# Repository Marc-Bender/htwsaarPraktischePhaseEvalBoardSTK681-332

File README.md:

# htwsaarPraktischePhaseEvalBoardSTK681-332
An Evaluation Board for the STK681-332-E Motor-driver IC by ON Semiconductor.
Designed as an add-on board to the arduino uno. Also designed as a concurrence "product" to the 
offical Evaluation-Board for the STK681-332-E IC with some enhanced features.

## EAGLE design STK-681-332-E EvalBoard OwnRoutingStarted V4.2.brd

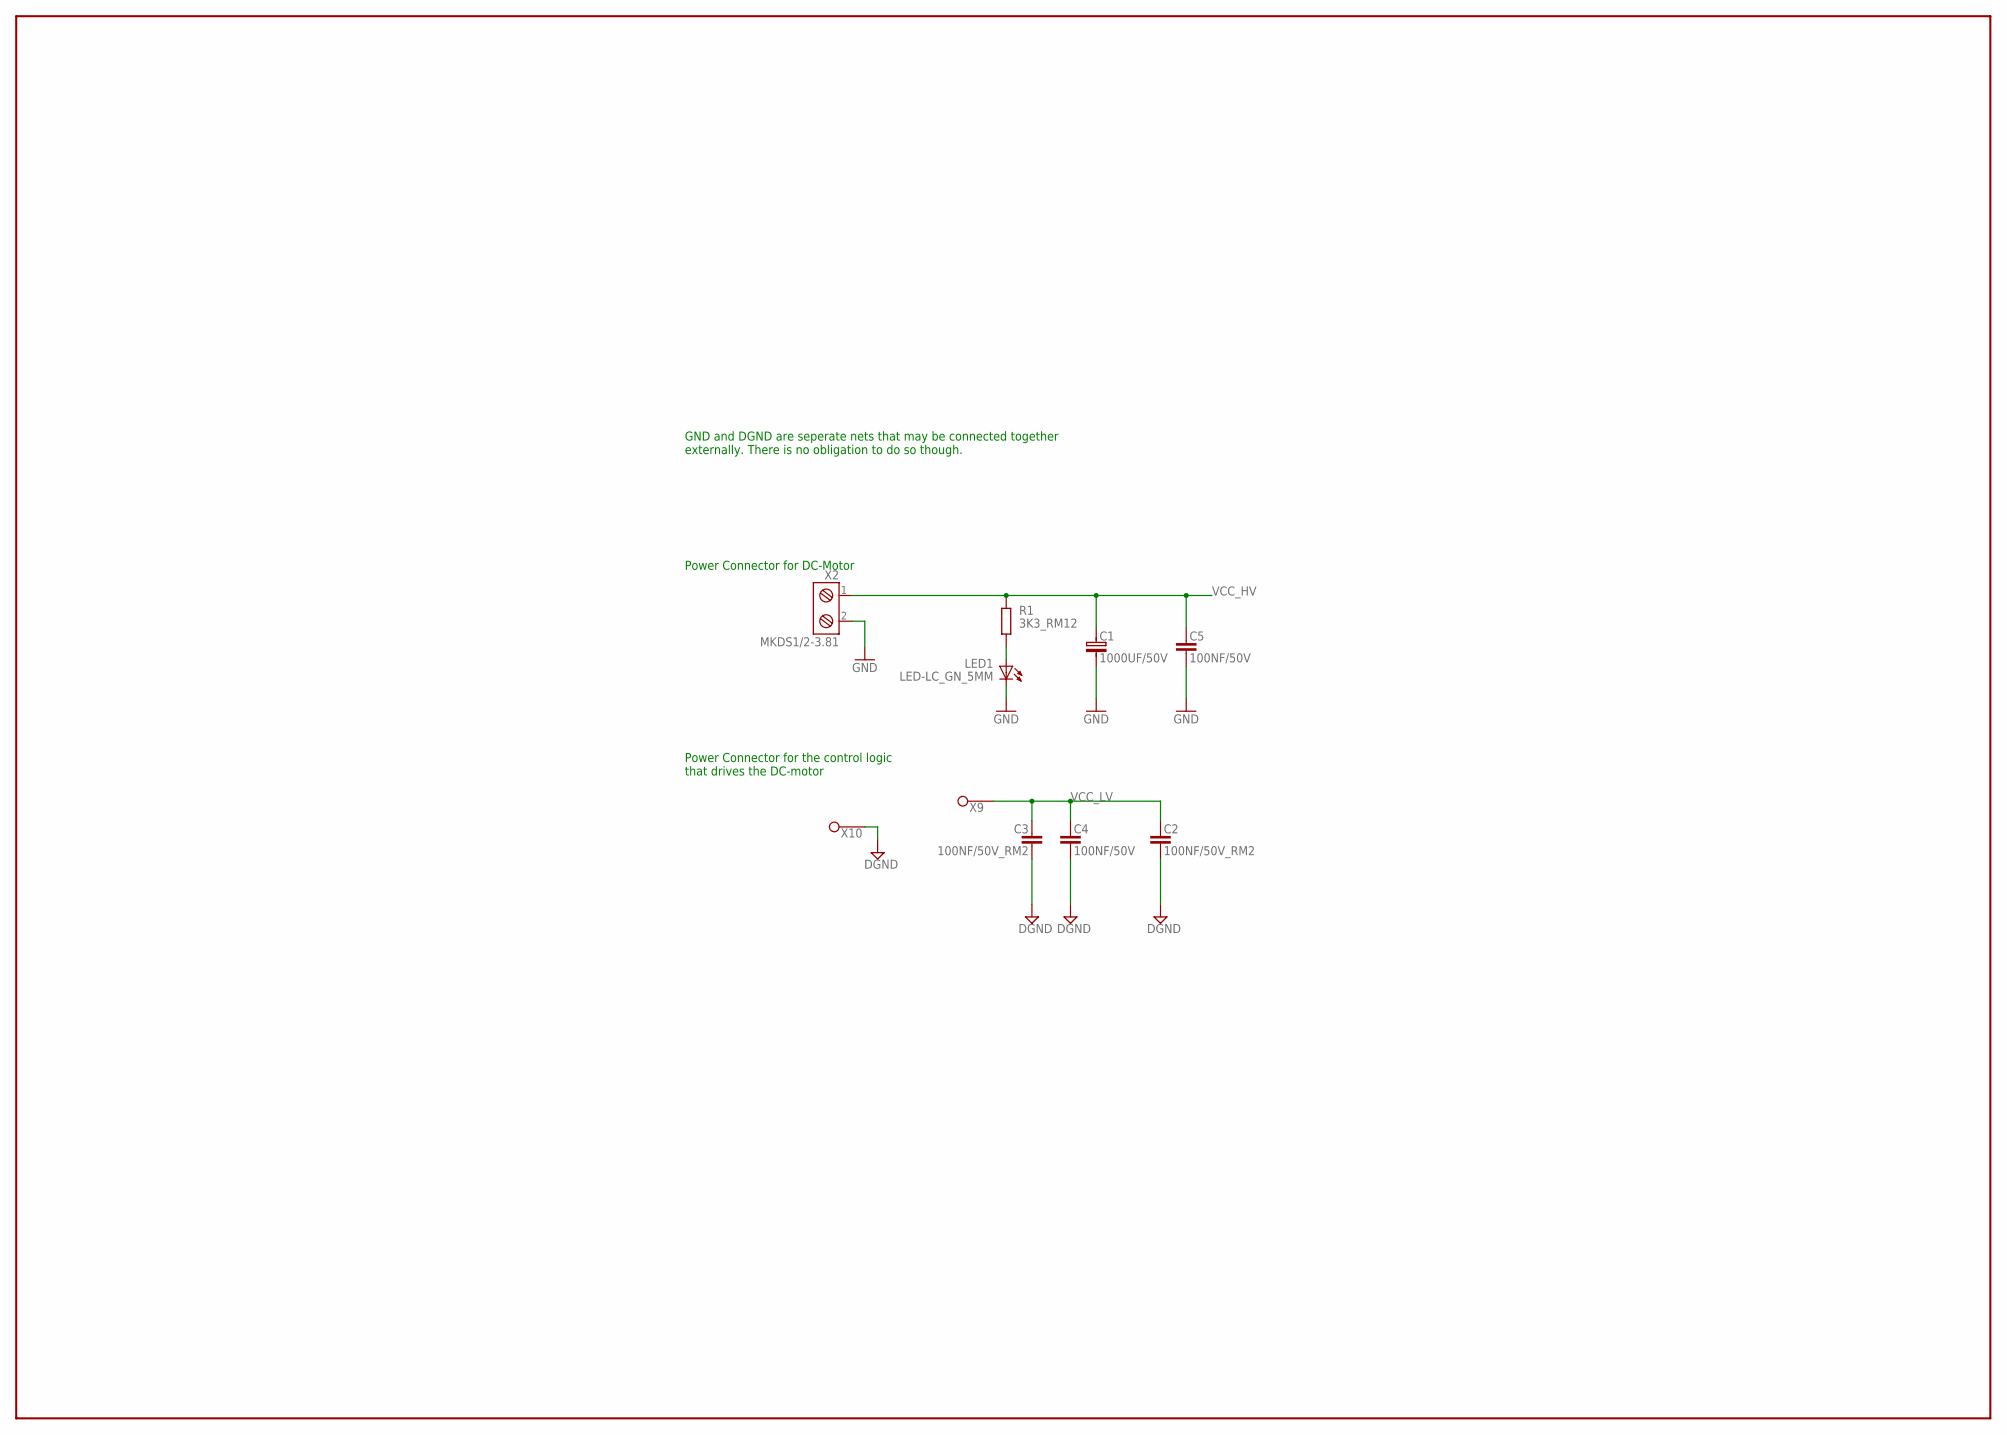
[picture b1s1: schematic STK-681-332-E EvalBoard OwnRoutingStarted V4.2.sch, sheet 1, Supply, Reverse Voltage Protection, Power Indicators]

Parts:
C1: 1000UF/50V; RM7,5D16
C2, C3: 100NF/50V_RM2; RM2.54
C4: 100NF/50V; 0603
C5: 100NF/50V; 1206
LED1: LED-LC_GN_5MM; LED5MM
R1: 3K3_RM12; RM12.7
X2: MKDS1/2-3.81
X9, X10: ST_1X1

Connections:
GND: C1.-, C2.2, C3.2, C4.2, C5.2, LED1.K (C), X2.2, X10.1; also elsewhere on the board
unnamed: LED1.A, R1.1
VCC_HV: C1.+, C5.1, R1.2, X2.1; also elsewhere on the board
VCC_LV: C2.1, C3.1, C4.1, X9.1; also elsewhere on the board

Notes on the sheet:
Power Connector for DC-Motor
GND and DGND are seperate nets that may be connected together externally. There is no obligation to do so though.
Power Connector for the control logic that drives the DC-motor

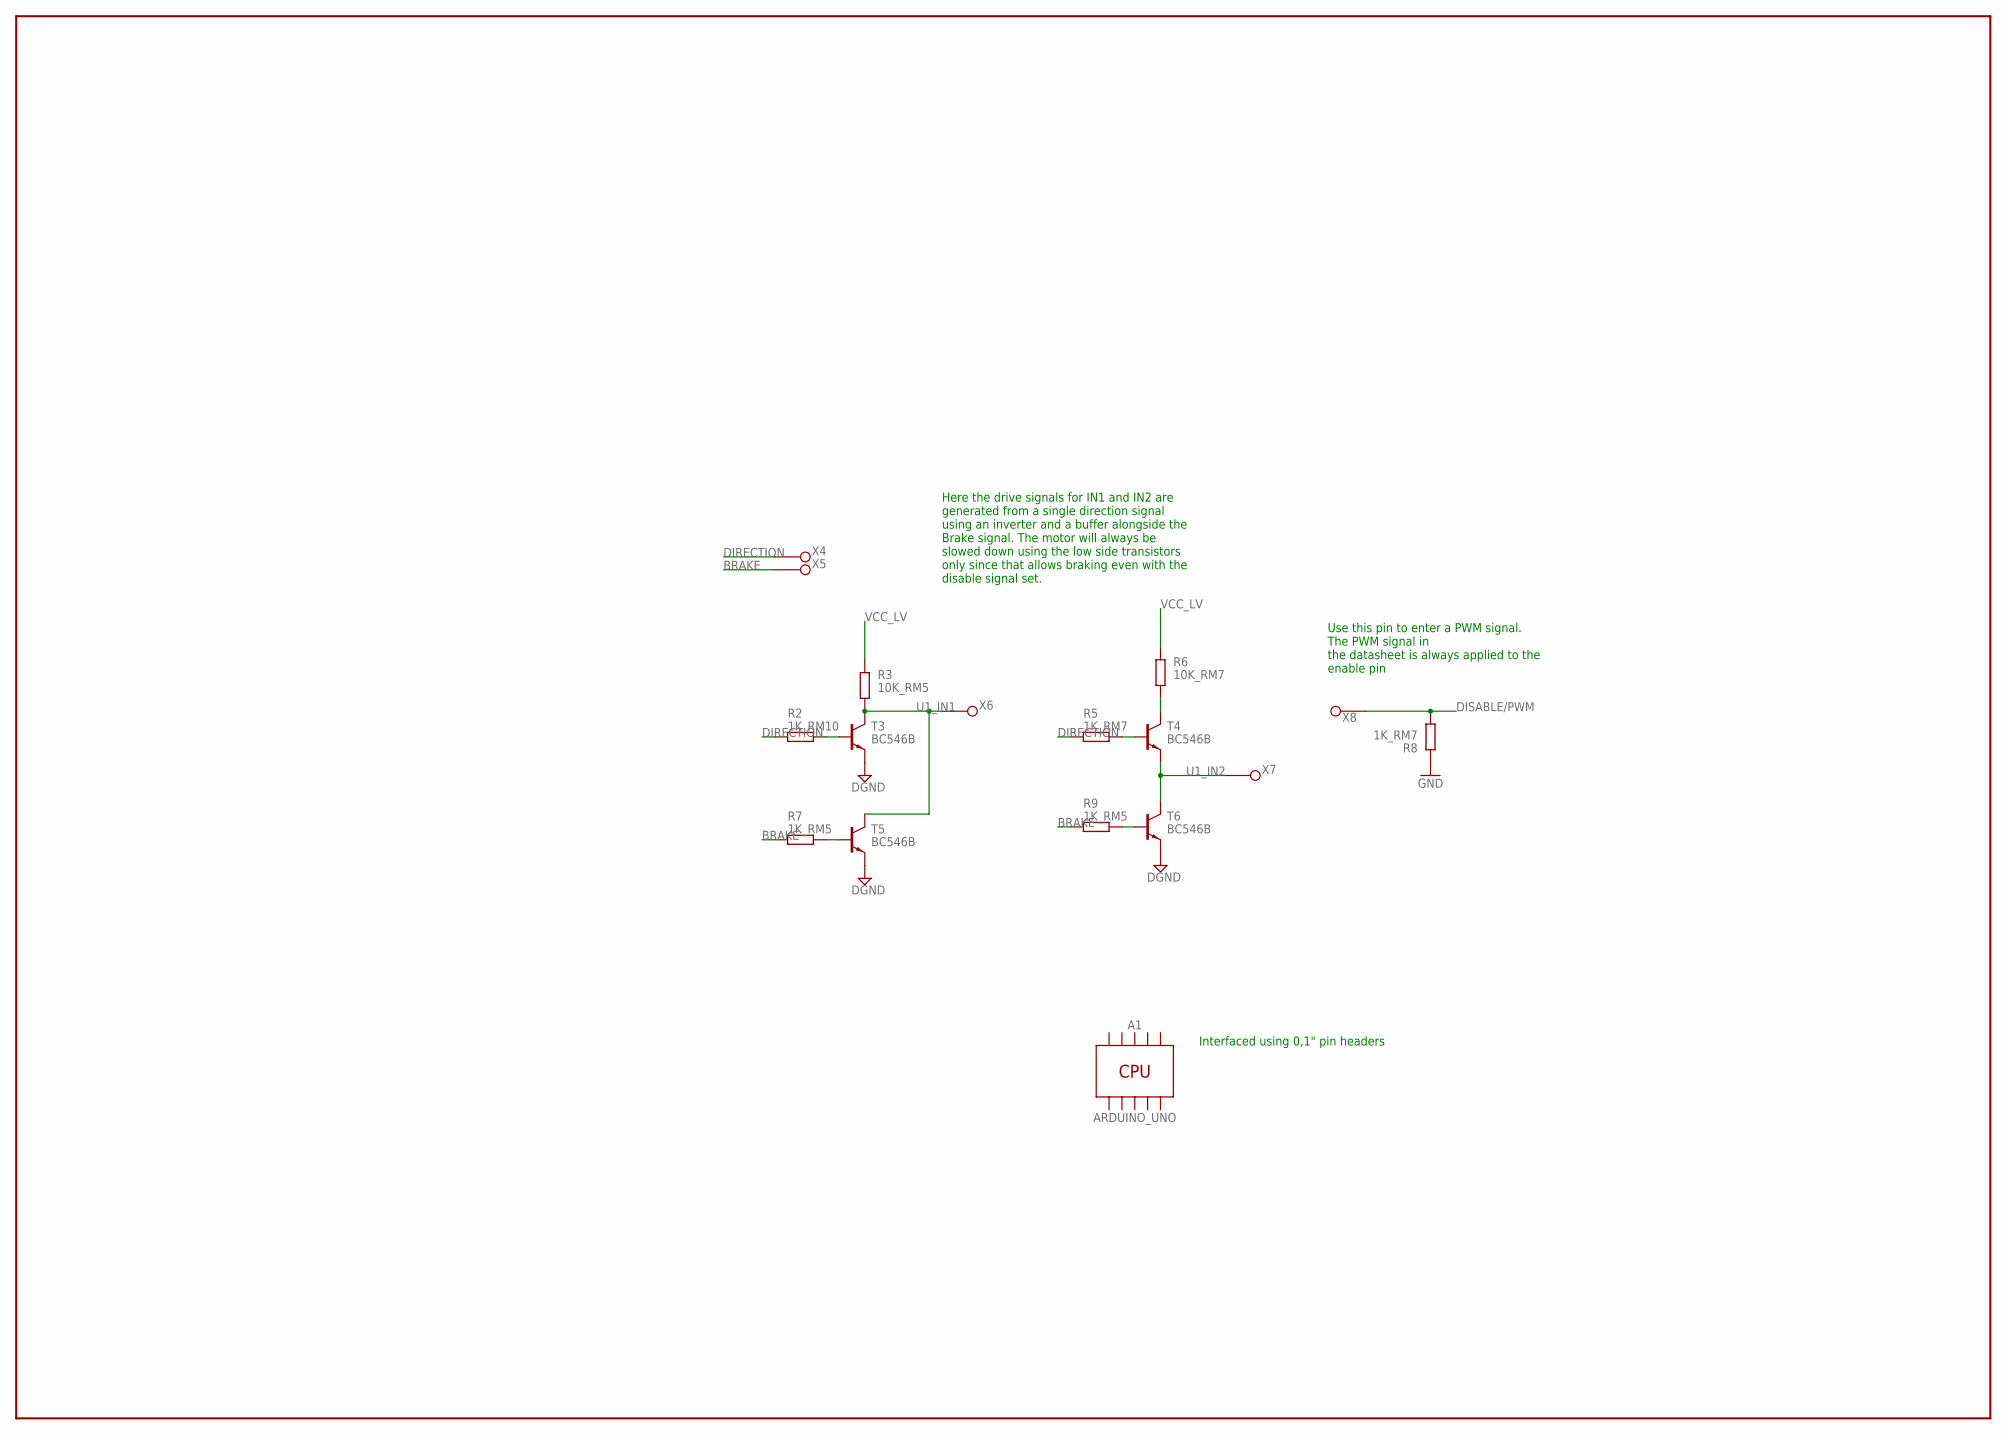
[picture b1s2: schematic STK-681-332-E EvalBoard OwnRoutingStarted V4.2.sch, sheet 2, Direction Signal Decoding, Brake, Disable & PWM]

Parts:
A1: ARDUINO_UNO
R2: 1K_RM10; RM10.16
R3: 10K_RM5; RM5.08
R5, R8: 1K_RM7; RM7.62
R6: 10K_RM7; RM7.62
R7, R9: 1K_RM5; RM5.08
T3, T4, T5, T6: BC546B; TO92
X4: DIRECTION; ST_1X1
X5: BRAKE; ST_1X1
X6: U1_IN1; ST_1X1
X7: U1_IN2; ST_1X1
X8: DISABLE_&_PWM; ST_1X1

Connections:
BRAKE: R7.1, R9.1, X5.1
DIRECTION: R2.1, R5.1, X4.1
DISABLE/PWM: R8.1, X8.1; also elsewhere on the board
GND: R8.2, T3.3 (E), T5.3 (E), T6.3 (E); also elsewhere on the board
unnamed: R2.2, T3.2 (B)
unnamed: R5.2, T4.2 (B)
unnamed: R6.1, T4.1 (C)
unnamed: R7.2, T5.2 (B)
unnamed: R9.2, T6.2 (B)
U1_IN1: R3.1, T3.1 (C), T5.1 (C), X6.1; also elsewhere on the board
U1_IN2: T4.3 (E), T6.1 (C), X7.1; also elsewhere on the board
VCC_LV: R3.2, R6.2; also elsewhere on the board

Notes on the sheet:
Here the drive signals for IN1 and IN2 are generated from a single direction signal using an inverter and a buffer alongside the Brake signal. The motor will always be slowed down using the low side transistors only since that allows braking even with the disable signal set.
Use this pin to enter a PWM signal. The PWM signal in the datasheet is always applied to the enable pin
Interfaced using 0,1" pin headers

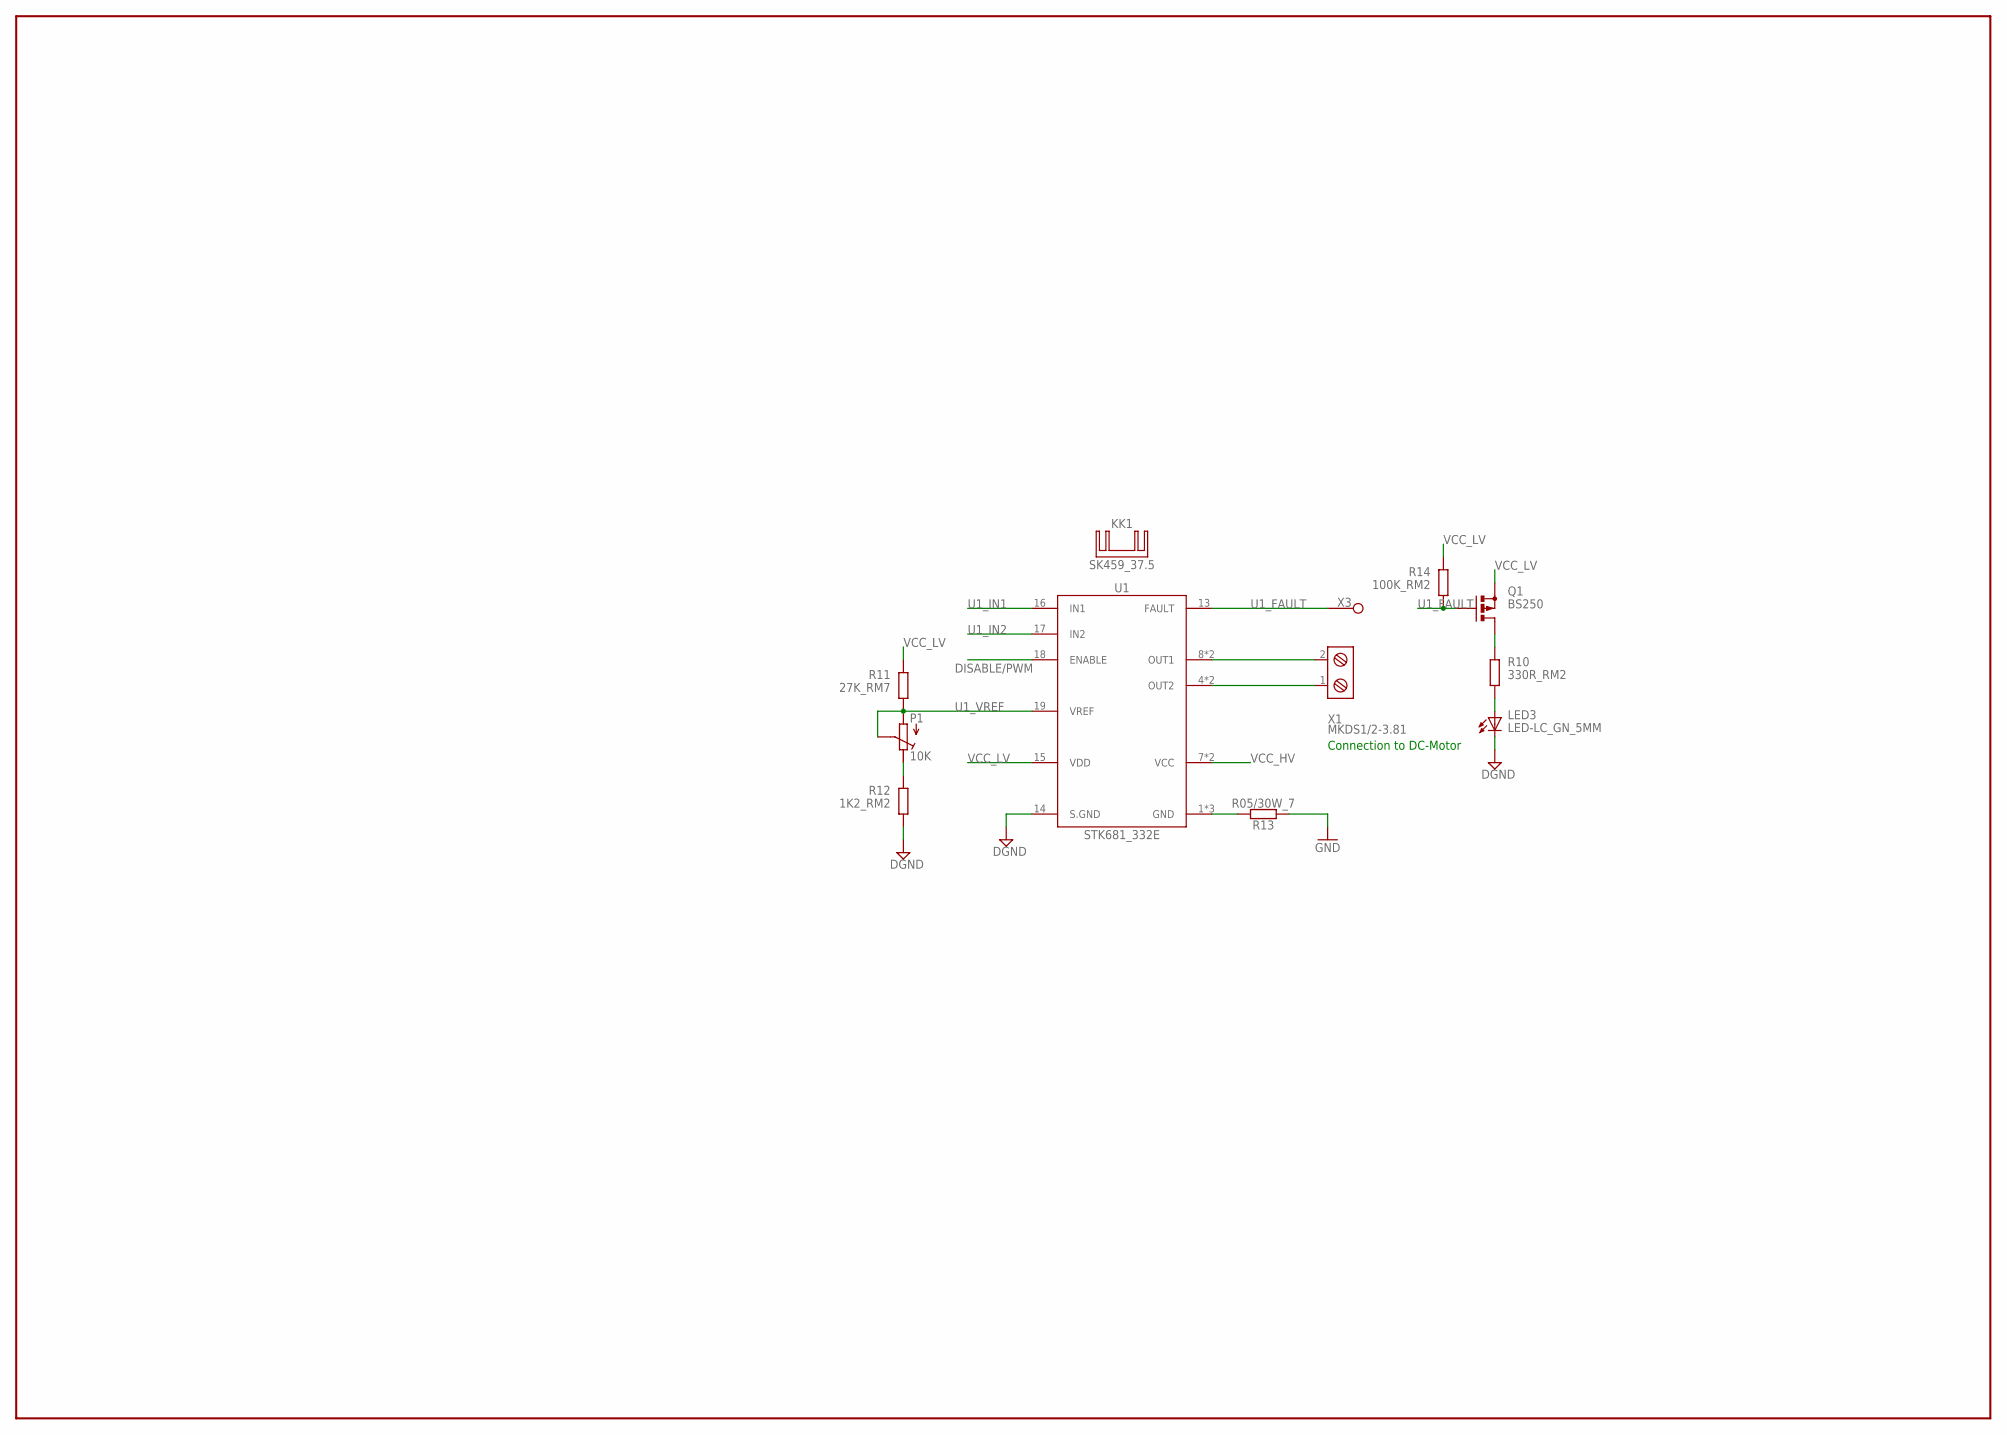
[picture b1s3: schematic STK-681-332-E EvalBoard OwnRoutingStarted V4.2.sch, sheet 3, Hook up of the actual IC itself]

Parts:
KK1: SK459_37.5; SK459
LED3: LED-LC_GN_5MM; LED5MM
P1: 10K; R_TRIMM
Q1: BS250; SOT54E
R10: 330R_RM2; RM2.54
R11: 27K_RM7; RM7.62
R12: 1K2_RM2; RM2.54
R13: R05/30W_7; TO220V/2_7
R14: 100K_RM2; RM2.54
U1: STK681_332E; SIP19
X1: MKDS1/2-3.81
X3: ST_1X1

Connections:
DISABLE/PWM: U1.18 (ENABLE); also elsewhere on the board
GND: LED3.K (C), R12.1, R13.1, U1.14 (S.GND); also elsewhere on the board
unnamed: U1.4 (OUT2), U1.6 (OUT2), X1.1
unnamed: U1.8 (OUT1), U1.10 (OUT1), X1.2
unnamed: LED3.A, R10.1
unnamed: Q1.D, R10.2
unnamed: P1.3 (E), R12.2
SENSE: R13.2, U1.1 (GND), U1.2 (GND), U1.3 (GND)
U1_FAULT: Q1.G, R14.1, U1.13 (FAULT), X3.1
U1_IN1: U1.16 (IN1); also elsewhere on the board
U1_IN2: U1.17 (IN2); also elsewhere on the board
U1_VREF: P1.1 (A), P1.2 (S), R11.1, U1.19 (VREF)
VCC_HV: U1.7 (VCC), U1.9 (VCC); also elsewhere on the board
VCC_LV: Q1.S, R11.2, R14.2, U1.15 (VDD); also elsewhere on the board

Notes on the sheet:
Connection to DC-Motor

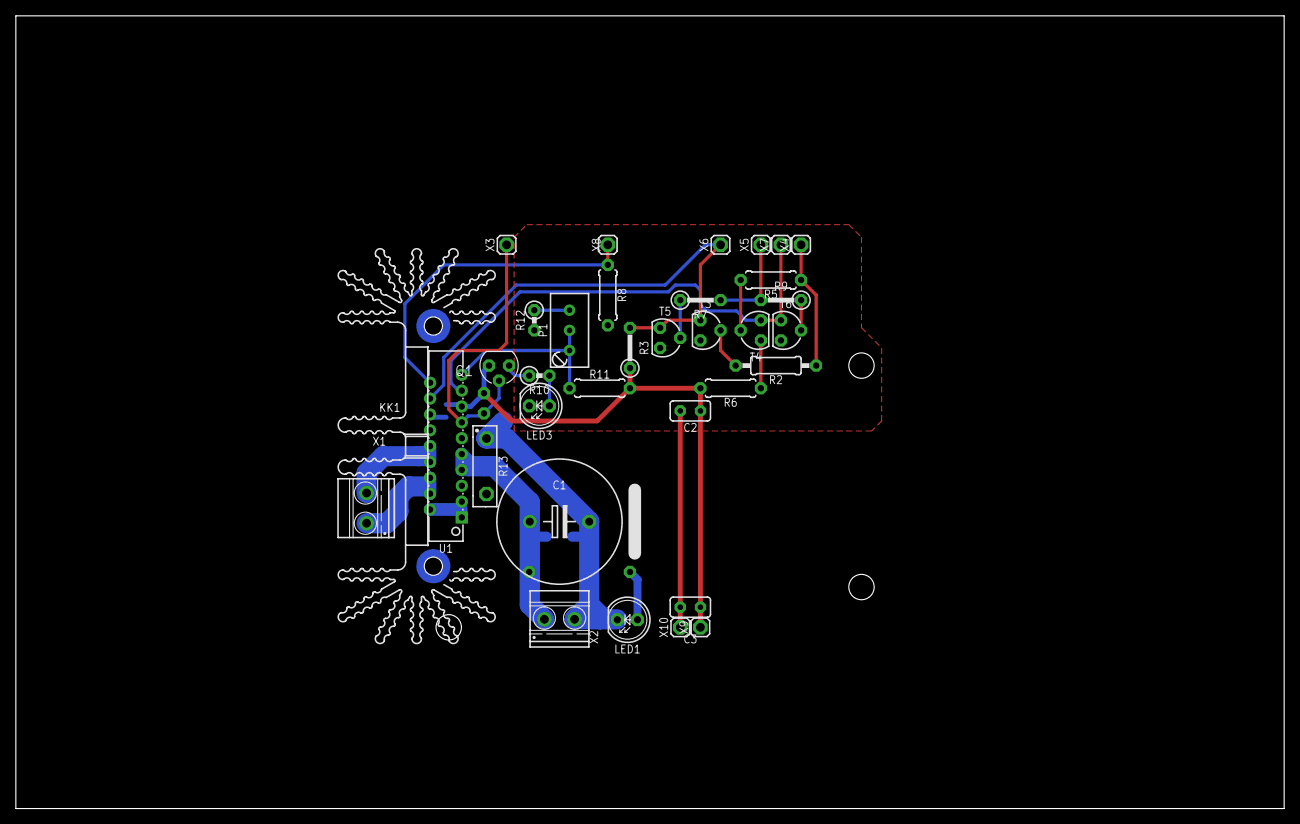
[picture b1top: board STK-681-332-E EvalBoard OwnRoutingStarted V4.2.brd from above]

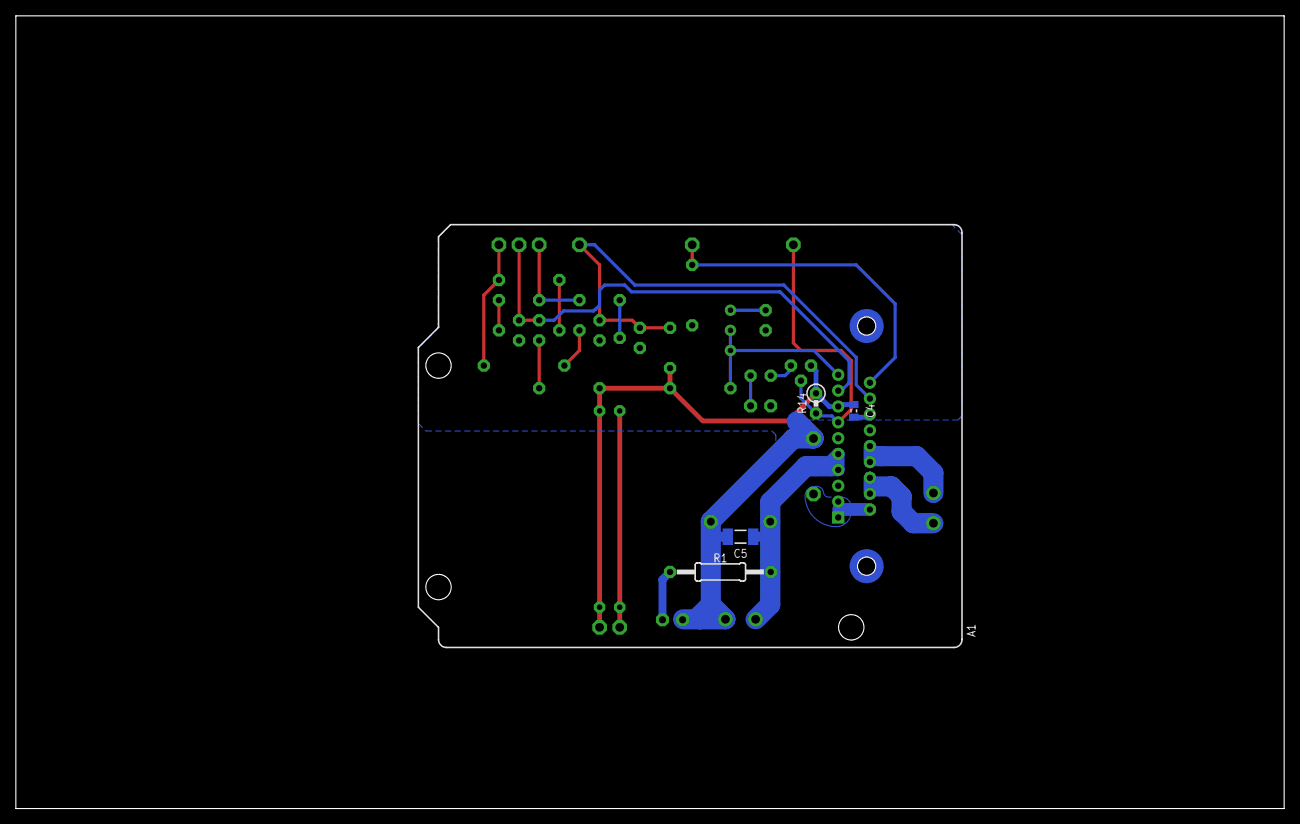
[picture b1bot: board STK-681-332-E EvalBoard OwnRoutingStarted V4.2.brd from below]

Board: 2 copper layers, 160.0 x 100.0 mm, 39 parts (5 on the bottom side), 22 nets.

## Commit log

2020-01-29 latest edition of the evaluation board
    known issue: used vin instead of the 5v pin for the underlaying Arduino uno base board. you may want to move and rotate LED 1 to make that pin accessible...
